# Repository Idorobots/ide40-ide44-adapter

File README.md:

# IDE 44 to IDE 40 adapter

This adapter makes it possible to connect old PATA 2.5" HDDs to 3.5" HDD slots. It's also smaller than most of the ones you can buy.

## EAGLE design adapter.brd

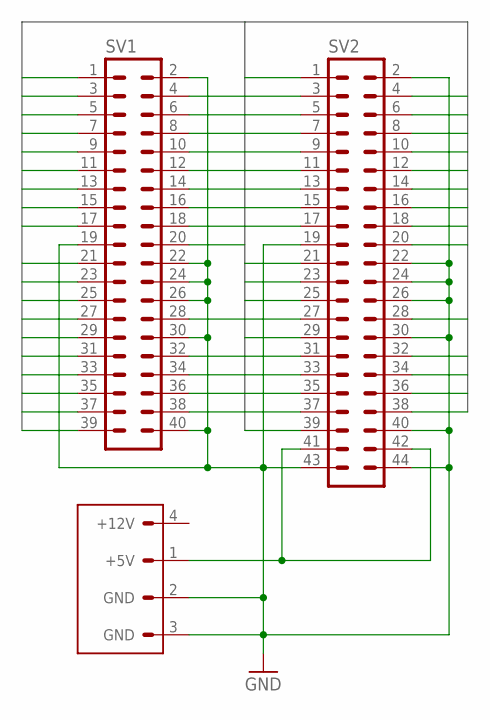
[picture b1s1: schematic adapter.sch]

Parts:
SV1: IDE40; ML40SMD
SV2: IDE44LOWPITCHF; PINHEAD2X22F
U$1: FLOPPYPWR

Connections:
GND: SV1.2 (GND), SV1.19 (GND), SV1.22 (GND), SV1.24 (GND), SV1.26 (GND), SV1.30 (GND), SV1.40 (GND), SV2.2 (GND), SV2.19 (GND), SV2.22 (GND), SV2.24 (GND), SV2.26 (GND), SV2.30 (GND), SV2.40 (GND), SV2.43 (GND), SV2.44 (!TYPE!), U$1.2 (GND), U$1.3 (GND)
IDE1: SV1.1 (!RESET!), SV2.1 (!RESET!)
IDE3: SV1.3 (D7), SV2.3 (D7)
IDE4: SV1.4 (D8), SV2.4 (D8)
IDE5: SV1.5 (D6), SV2.5 (D6)
IDE6: SV1.6 (D9), SV2.6 (D9)
IDE7: SV1.7 (D5), SV2.7 (D5)
IDE8: SV1.8 (D10), SV2.8 (D10)
IDE9: SV1.9 (D4), SV2.9 (D4)
IDE10: SV1.10 (D11), SV2.10 (D11)
IDE11: SV1.11 (D3), SV2.11 (D3)
IDE12: SV1.12 (D12), SV2.12 (D12)
IDE13: SV1.13 (D2), SV2.13 (D2)
IDE14: SV1.14 (D13), SV2.14 (D13)
IDE15: SV1.15 (D1), SV2.15 (D1)
IDE16: SV1.16 (D14), SV2.16 (D14)
IDE17: SV1.17 (D0), SV2.17 (D0)
IDE18: SV1.18 (D15), SV2.18 (D15)
IDE20: SV1.20 (KEY), SV2.20 (KEY)
IDE21: SV1.21 (DMARQ), SV2.21 (DMARQ)
IDE23: SV1.23 (!IOW!), SV2.23 (!IOW!)
IDE25: SV1.25 (!IOR!), SV2.25 (!IOR!)
IDE27: SV1.27 (IORDY), SV2.27 (IORDY)
IDE28: SV1.28 (CSEL), SV2.28 (CSEL)
IDE29: SV1.29 (!DMACK!), SV2.29 (!DMACK!)
IDE31: SV1.31 (INTRQ), SV2.31 (INTRQ)
IDE32: SV1.32 (!IOCS16!), SV2.32 (!IOCS16!)
IDE33: SV1.33 (A1), SV2.33 (A1)
IDE34: SV1.34 (DIAG), SV2.34 (DIAG)
IDE35: SV1.35 (A0), SV2.35 (A0)
IDE36: SV1.36 (A2), SV2.36 (A2)
IDE37: SV1.37 (!CS0!), SV2.37 (!CS0!)
IDE38: SV1.38 (!CS1!), SV2.38 (!CS1!)
IDE39: SV1.39 (!ACTIVE!), SV2.39 (!ACTIVE!)
unnamed: SV2.41 (VCC), SV2.42 (VCC), U$1.1 (+5V)

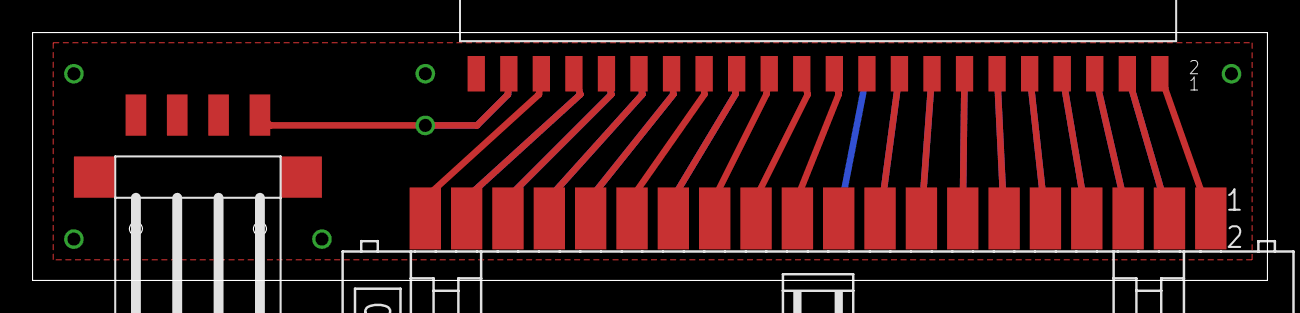
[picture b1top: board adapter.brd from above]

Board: 2 copper layers, 75.9 x 15.2 mm, 3 parts (0 on the bottom side), 35 nets.

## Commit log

2016-04-11 Added a library with connectors used in this adapter.
2016-04-11 Added the schematic of the adapter.
2016-04-11 Connected the ground together.
2016-04-11 Added a PCB layout.
2016-04-11 Reduced pin pitch on the IDE 44 connector.
2016-04-11 Added more space for the power plug.
2016-04-11 Improved the PCB layout a little.
2016-04-18 Adjusted the board layout.
2016-04-18 Added a .gitignore.
2016-04-18 Added a README.
